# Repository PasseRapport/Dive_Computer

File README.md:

# Freediving Computer

A wrist-mounted freediving computer with tap navigation, wireless charging, and a fully sealed enclosure — no buttons, no external connectors.

---

## V1 — Proof of Concept

Proved two core ideas: **tap-based navigation** via accelerometer and **wireless charging** inside a completely sealed case.

| | |
|---|---|
| **MCU** | ESP32-C3 |
| **Display** | 1.27″ SSD1351 color OLED (128×96) |
| **Pressure** | MS5837-30BA — ±2 mm resolution |
| **Navigation** | LIS2DUX12 tap detection — no buttons |
| **Charging** | LTC4120 wireless receiver — no connectors |
| **Switch** | Magnetic battery cutoff — true 0 µA storage |

### Interface

<p align="center"><em>Tap-based menu navigation — accelerometer detects directional impacts on the casing.</em></p>

### In the Water

<p align="center"><em>Live depth tracking — automatic dive detection and surface recovery timer.</em></p>

### Enclosure

Two-part sandwich assembly sealed by a perimeter O-ring and 12 M2 screws. No dynamic seals anywhere.

---

## V2 — Work in Progress

More compact, better component integration, and additional sensors.

### PCB

### 3D Model

### Exploded View

### Schematic

---

## Repository Structure

```
Dive_Computer/
├── V1/         # Prototype — full firmware + hardware source files
└── V2/         # Current revision — in progress
```

See [`V1/README.md`](V1/README.md) for detailed hardware architecture, firmware design, and dive state machine documentation.

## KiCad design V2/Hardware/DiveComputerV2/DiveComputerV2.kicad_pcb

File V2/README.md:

# Freediving Computer V2

## 3D

## Exploded View

## PCB

## Schematic

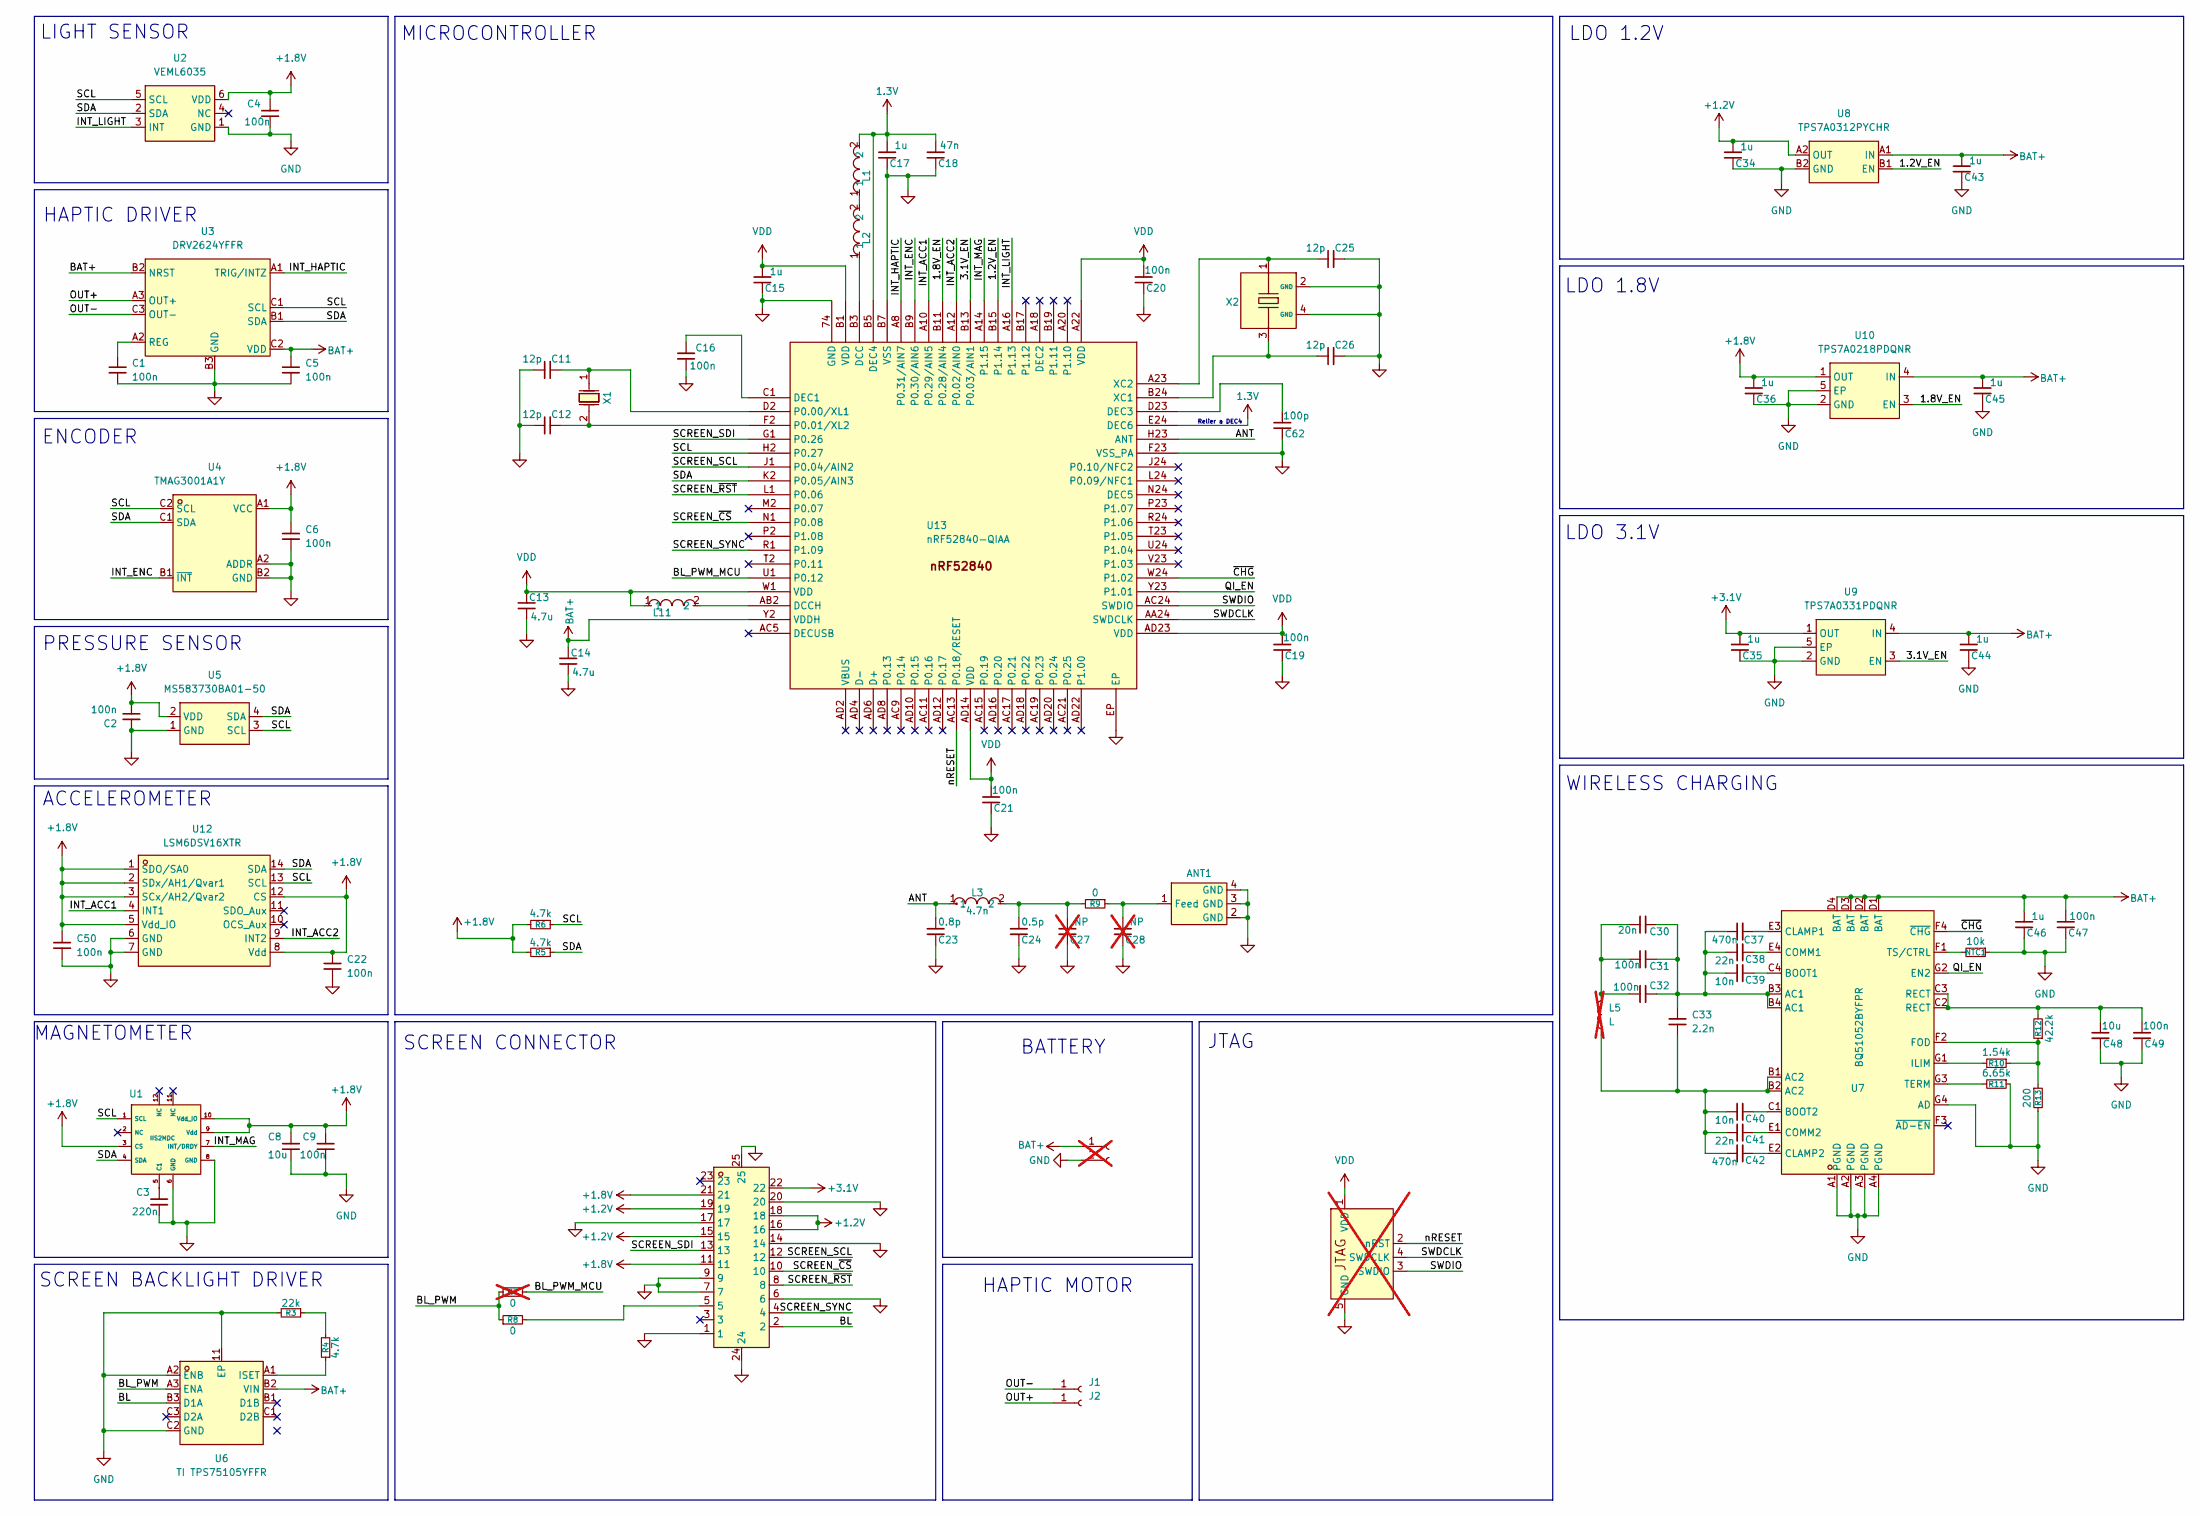
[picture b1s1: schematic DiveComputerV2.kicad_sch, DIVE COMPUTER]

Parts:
ANT1: 2450AT18D0100E; ANT-SMD_4P-L3.2-W1.6; MPN 2450AT18D0100E; LCSC Part C2917718
C1, C2, C4, C5, C6, C9, C22, C47, C50: 100n; C_0402_1005Metric; MPN CL05B104KO5NNNC; LCSC Part C1525
C3: 220n; C_0402_1005Metric; MPN CL05B224KO5NNNC; LCSC Part C16772
C8: 10u; C_0402_1005Metric; LCSC Part C15525
C11, C12, C25, C26: 12p; C_0402_1005Metric; MPN 0402CG120J500NT; LCSC Part C1547
C13, C14: 4.7u; C_0402_1005Metric; LCSC Part C23733
C15, C34, C35, C36, C43, C44, C45, C46: 1u; C_0402_1005Metric; MPN CL05A105KA5NQNC; LCSC Part C52923
C16, C19, C20, C21, C49: 100n; C_0402_1005Metric; MPN CL05B104KB54PNC; LCSC Part C307331
C17: 1u; C_0402_1005Metric; MPN TCC0402X7R105K250AT; LCSC Part C53426846
C18: 47n; C_0402_1005Metric; MPN CL05B473KO5NNNC; LCSC Part C307434
C23: 0.8p; C_0402_1005Metric; MPN GJM1555C1HR80WB01D; LCSC Part C88902
C24: 0.5p; C_0402_1005Metric; MPN GJM1555C1HR50WB01D; LCSC Part C76912
C27, C28: NP; C_0402_1005Metric; not fitted
C30: 20n; C_0805_2012Metric; Voltage 50V; Tolerance 1%; MPN GCM21B5C1H203FA16L; LCSC Part C17588990
C31, C32: 100n; C_1206_3216Metric; Voltage 50V; Tolerance 5%; MPN GRM31C5C1H104JA01L; LCSC Part C97946
C33: 2.2n; C_0402_1005Metric; MPN GRM1555C1H222GA01D; LCSC Part C2987940
C37, C42: 470n; C_0402_1005Metric; MPN GRM155R61E474KE01D; LCSC Part C437526
C38, C41: 22n; C_0402_1005Metric; MPN 0402B223K500NT; LCSC Part C1532
C39, C40: 10n; C_0402_1005Metric; MPN GRM155R71H103KA88J; LCSC Part C2840480
C48: 10u; C_0603_1608Metric; MPN CL10A106MA8NRNC; LCSC Part C96446
C62: 100p; C_0402_1005Metric; MPN 0402CG101J500NT; LCSC Part C1546
FPC1: FH35C-23S-0.3SHW; FPC-SMD_23P-P0.60_HRS_FH35C-23S-0.3SHW; MPN FH35C-23S-0.3SHW(50); LCSC Part C2889270
J1, J2: Conn_01x01_Socket; 2292838-3
J3: Conn_01x02_Socket; THT Solder PAD 2pin; not fitted
J5: SAH_Connect; not fitted
L1: LQW15AN15NG00D; IND-SMD_L1.0-W0.5-2; MPN LQW15AN15NG00D; LCSC Part C98055
L2: LQM18DN100M70L; L0603; MPN LQM18DN100M70L; LCSC Part C713281
L3: 4.7n; L0402-RD; MPN LQG15HS4N7B02D; LCSC Part C162543
L5: L; THT Solder PAD 2pin; not fitted
L11: SLM1608100MIT; L_0603_1608Metric; MPN SLM1608100MIT; LCSC Part C2831366
NTC1: 10k; R_0402_1005Metric; MPN NCP15XH103F03RC; LCSC Part C77131
R3: 22k; R_0402_1005Metric; MPN 0402WGF2202TCE; LCSC Part C25768
R4, R5, R6: 4.7k; R_0402_1005Metric; MPN 0402WGF4701TCE; LCSC Part C25900
R7: 0; R_0402_1005Metric; LCSC Part C17168; not fitted
R8, R9: 0; R_0402_1005Metric; LCSC Part C17168
R10: 1.54k; R_0402_1005Metric; MPN CRCW04021K54FKED; LCSC Part C2085404
R11: 6.65k; R_0402_1005Metric; MPN CRCW04026K65FKED; LCSC Part C2076542
R12: 42.2k; R_0402_1005Metric; MPN FRC0402F4222TS; LCSC Part C5126131
R13: 200; R_0402_1005Metric; MPN 0402WGF2000TCE; LCSC Part C25087
U1: IIS2MDC; VLGA-12_L2.0-W2.0-P0.50-BL; MPN IIS2MDCTR; LCSC Part C2655002
U2: VEML6035; SMD-6_L2.0-W2.0-P0.65-BL; MPN VEML6035; LCSC Part C2655158
U3: DRV2624YFFR; DSBGA-9_L1.4-W1.3-R3-C3-P0.40-BL; MPN DRV2624YFFR; LCSC Part C881487
U4: TMAG3001A1Y; BGA-6_L1.3-W0.8-P0.40-TL_PTMAG3001A2YBGR; MPN TMAG3001A1YBGR; LCSC Part C29073186
U5: MS583730BA01-50; SENSOR-SMD_4P-L3.3-W3.3-P2.00-BL; MPN MS583730BA01-50; LCSC Part C2887941
U6: TI TPS75105YFFR; DSBGA-9_L1.4-W1.3-R3-C3-P0.40-BL; MPN TI TPS75105YFFR; LCSC Part C1857508
U7: BQ51052BYFPR; DSBGA-28_L3.0-W1.9-R4-C7-P0.40-BL; MPN BQ51052BYFPR; LCSC Part C2155980
U8: TPS7A0312PYCHR; DSBGA-4_L0.7-W0.7-R2-C2-P0.35-BL; MPN TPS7A0312PYCHR; LCSC Part C3747308
U9: TPS7A0331PDQNR; X2SON-4_L1.0-W1.0-P0.65-TL-EP; MPN TPS7A0331PDQNR; LCSC Part C2864441
U10: TPS7A0218PDQNR; X2SON-4_L1.0-W1.0-P0.65-TL-EP; MPN TPS7A0218PDQNR; LCSC Part C2862166
U12: LSM6DSV16XTR; LGA-14_L3.0-W2.5-P0.50-BR; MPN LSM6DSV16XTR; LCSC Part C5267406
U13: nRF52840-QIAA; Nordic_AQFN-73-1EP_7x7mm_P0.5mm; PART NUMBER nRF52840-QIAA
X1: CM8V-T1A-32.768KHZ-9PF-20PPM-TB-QC; CRYSTAL-SMD_L2.0-W1.2; MPN CM8V-T1A-32.768kHz-9pF-20PPM-TB-QC; LCSC Part C5280691
X2: ECS-320-CDX-2152; CRYSTAL-SMD_4P-L1.6-W1.2-BL; MPN ECS-320-CDX-2152; LCSC Part C5686354

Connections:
1.3V: C17.2, C18.2, L1.2, U13.B5 (DEC4), U13.E24 (DEC6)
+1.2V: C34.2, FPC1.15, FPC1.16, FPC1.18, FPC1.19, U8.A2 (OUT)
+1.8V: C2.2, C4.1, C6.2, C8.1, C9.1, C22.1, C36.2, C50.2, FPC1.11, FPC1.21, R5.2, R6.2, U1.3 (CS), U1.9 (Vdd), U1.10 (Vdd_IO), U2.6 (VDD), U4.A1 (VCC), U5.2 (VDD), U10.1 (OUT), U12.1 (SDO/SA0), U12.2 (SDx/AH1/Qvar1), U12.3 (SCx/AH2/Qvar2), U12.5 (Vdd_IO), U12.8 (Vdd), U12.12 (CS)
+3.1V: C35.2, FPC1.22, U9.1 (OUT)
/1.2V_EN: U8.B1 (EN), U13.B15 (P1.14)
/1.8V_EN: U10.3 (EN), U13.B11 (P0.28/AIN4)
/3.1V_EN: U9.3 (EN), U13.B13 (P0.03/AIN1)
/ANT: C23.2, L3.1, U13.H23 (ANT)
/BL: FPC1.2, U6.B3 (D1A)
/BL_PWM: R7.1, R8.1, U6.A3 (ENA)
/BL_PWM_MCU: R7.2, U13.U1 (P0.12)
/INT_ACC1: U12.4 (INT1), U13.A10 (P0.29/AIN5)
/INT_ACC2: U12.9 (INT2), U13.A12 (P0.02/AIN0)
/INT_ENC: U4.B1 (~INT), U13.B9 (P0.30/AIN6)
/INT_HAPTIC: U3.A1 (TRIG/INTZ), U13.A8 (P0.31/AIN7)
/INT_LIGHT: U2.3 (INT), U13.A16 (P1.13)
/INT_MAG: U1.7 (INT/DRDY), U13.A14 (P1.15)
/OUT+: J2.1 (Pin_1_1), U3.A3 (OUT+)
/OUT-: J1.1 (Pin_1_1), U3.C3 (OUT-)
/QI_EN: U7.G2 (EN2), U13.Y23 (P1.01)
/SCL: R6.1, U1.1 (SCL), U2.5 (SCL), U3.C1 (SCL), U4.C2 (SCL), U5.3 (SCL), U12.13 (SCL), U13.H2 (P0.27)
/SCREEN_SCL: FPC1.12, U13.J1 (P0.04/AIN2)
/SCREEN_SDI: FPC1.13, U13.G1 (P0.26)
/SCREEN_SYNC: FPC1.4, U13.R1 (P1.09)
/SCREEN_~CS: FPC1.10, U13.N1 (P0.08)
/SCREEN_~RST: FPC1.8, U13.L1 (P0.06)
/SDA: R5.1, U1.4 (SDA), U2.2 (SDA), U3.B1 (SDA), U4.C1 (SDA), U5.4 (SDA), U12.14 (SDA), U13.K2 (P0.05/AIN3)
/SWDCLK: J5.4 (SWDCLK), U13.AA24 (SWDCLK)
/SWDIO: J5.3 (SWDIO), U13.AC24 (SWDIO)
/nRESET: J5.2 (nRST), U13.AC13 (P0.18/RESET)
/~CHG: U7.F4 (~CHG), U13.W24 (P1.02)
BAT+: C5.1, C14.1, C43.2, C44.2, C45.2, C46.2, C47.2, J3.1, U3.B2 (NRST), U3.C2 (VDD), U6.B2 (VIN), U7.D1 (BAT), U7.D2 (BAT), U7.D3 (BAT), U7.D4 (BAT), U8.A1 (IN), U9.4 (IN), U10.4 (IN), U13.Y2 (VDDH)
GND: ANT1.2 (GND), ANT1.3 (GND), ANT1.4 (GND), C1.2, C2.1, C3.2, C4.2, C5.2, C6.1, C8.2, C9.2, C11.2, C12.2, C13.2, C14.2, C15.1, C16.2, C17.1, C18.1, C19.1, C20.1, C21.1, C22.2, C23.1, C24.1, C25.1, C26.1, C27.1, C28.1, C34.1, C35.1, C36.1, C43.1, C44.1, C45.1, C46.1, C47.1, C48.1, C49.1, C50.1, C62.1, FPC1.1, FPC1.6, FPC1.7, FPC1.9, FPC1.14, FPC1.17, FPC1.20, FPC1.24, FPC1.25, J3.2, J5.5 (GND), NTC1.1, R3.2, R11.1, R13.2, U1.6 (GND), U1.8 (GND), U2.1 (GND), U3.B3 (GND), U4.A2 (ADDR), U4.B2 (GND), U5.1 (GND), U6.11 (EP), U6.A2 (ENB), U6.C2 (GND), U7.A1 (PGND), U7.A2 (PGND), U7.A3 (PGND), U7.A4 (PGND), U7.G4 (AD), U8.B2 (GND), U9.2 (GND), U9.5 (EP), U10.2 (GND), U10.5 (EP), U12.6 (GND), U12.7 (GND), U13.74 (GND), U13.B7 (VSS), U13.EP, U13.F23 (VSS_PA), X2.2 (GND), X2.4 (GND)
unnamed: ANT1.1 (Feed), C28.2, R9.1
unnamed: C24.2, C27.2, L3.2, R9.2
unnamed: C30.1, C31.1, C32.1, L5.2
unnamed: C30.2, C31.2, C32.2, C33.1, C37.1, C38.1, C39.1, U7.B3 (AC1), U7.B4 (AC1)
unnamed: C33.2, C40.1, C41.1, C42.1, L5.1, U7.B1 (AC2), U7.B2 (AC2)
unnamed: C48.2, C49.2, R12.2, U7.C2 (RECT), U7.C3 (RECT)
unnamed: FPC1.5, R8.2
unnamed: L1.1, L2.2
unnamed: R3.1, R4.2
unnamed: C3.1, U1.5 (C1)
unnamed: C1.1, U3.A2 (REG)
unnamed: R4.1, U6.A1 (ISET)
unnamed: C39.2, U7.C4 (BOOT1)
unnamed: C40.2, U7.C1 (BOOT2)
unnamed: C37.2, U7.E3 (CLAMP1)
unnamed: C42.2, U7.E2 (CLAMP2)
unnamed: C38.2, U7.E4 (COMM1)
unnamed: C41.2, U7.E1 (COMM2)
unnamed: R10.1, R12.1, R13.1, U7.F2 (FOD)
unnamed: R10.2, U7.G1 (ILIM)
unnamed: R11.2, U7.G3 (TERM)
unnamed: NTC1.2, U7.F1 (TS/CTRL)
unnamed: L2.1, U13.B3 (DCC)
unnamed: L11.2, U13.AB2 (DCCH)
unnamed: C16.1, U13.C1 (DEC1)
unnamed: C62.2, U13.D23 (DEC3)
unnamed: C11.1, U13.D2 (P0.00/XL1), X1.1
unnamed: C12.1, U13.F2 (P0.01/XL2), X1.2
unnamed: C26.2, U13.B24 (XC1), X2.3
unnamed: C25.2, U13.A23 (XC2), X2.1
VDD: C13.1, C15.2, C19.2, C20.2, C21.2, J5.1 (VDD), L11.1, U13.A22 (VDD), U13.AD14 (VDD), U13.AD23 (VDD), U13.B1 (VDD), U13.W1 (VDD)

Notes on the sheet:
PRESSURE SENSOR
MICROCONTROLLER
SCREEN BACKLIGHT DRIVER
BATTERY
SCREEN CONNECTOR
Relier a DEC4
ACCELEROMETER
HAPTIC MOTOR
JTAG
ENCODER
LDO 1.8V
WIRELESS CHARGING
HAPTIC DRIVER
LDO 3.1V
LDO 1.2V
MAGNETOMETER
LIGHT SENSOR

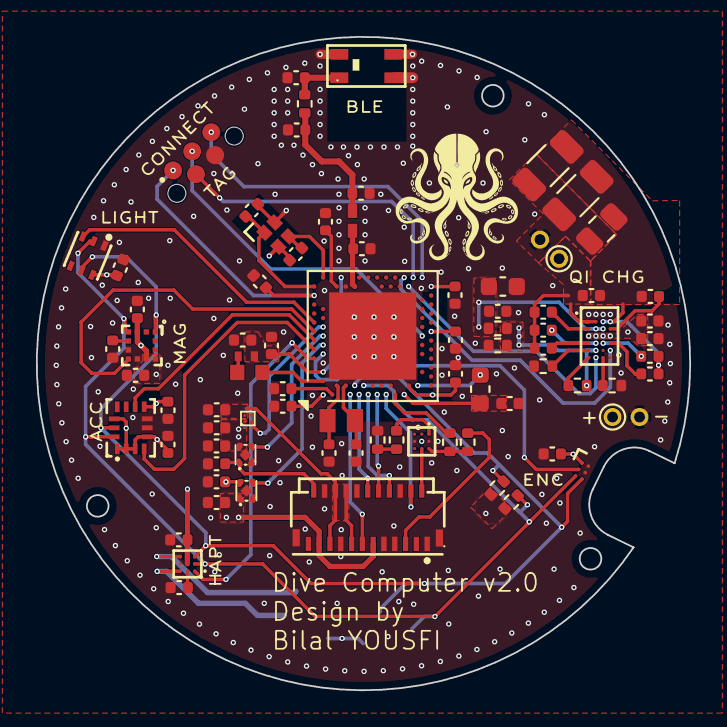
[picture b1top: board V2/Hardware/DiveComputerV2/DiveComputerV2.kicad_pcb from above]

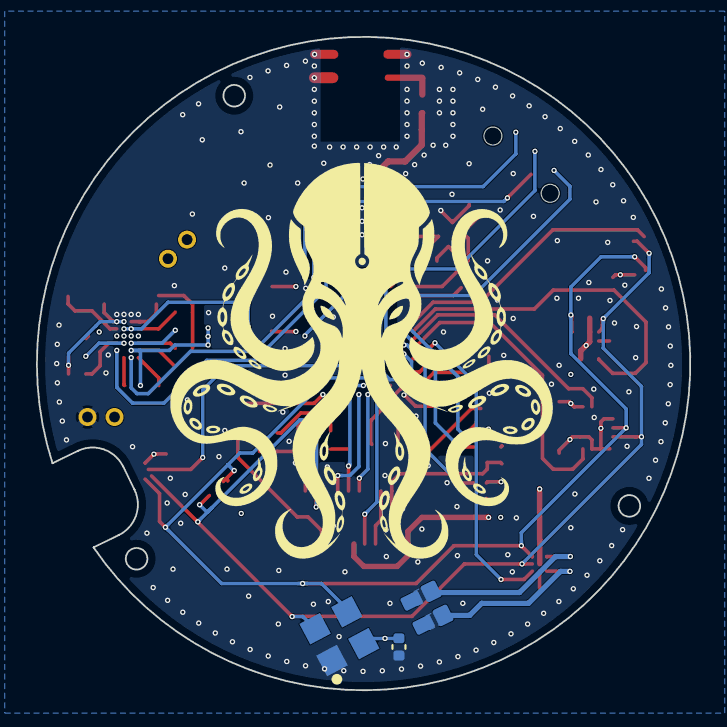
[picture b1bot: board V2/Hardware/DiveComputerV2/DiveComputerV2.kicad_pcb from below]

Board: 4 copper layers, 36.3 x 36.3 mm, 85 parts (4 on the bottom side), 64 nets.

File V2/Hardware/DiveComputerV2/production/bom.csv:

Designator,Footprint,Quantity,Value,LCSC Part #
ANT1,ANT-SMD_4P-L3.2-W1.6,1,2450AT18D0100E,C2917718
"C1, C2, C22, C4, C47, C5, C50, C6, C9",0402,9,100n,C1525
"C11, C12, C25, C26",0402,4,12p,C1547 
"C13, C14",0402,2,4.7u,C23733
"C15, C34, C35, C36, C43, C44, C45, C46",0402,8,1u,C52923
"C16, C19, C20, C21, C49",0402,5,100n,C307331
C17,0402,1,1u,C53426846
C18,0402,1,47n,C307434
C23,0402,1,0.8p,C88902
C24,0402,1,0.5p,C76912
C3,0402,1,220n,C16772
C30,0805,1,20n,C17588990
"C31, C32",1206,2,100n,C97946
C33,0402,1,2.2n,C2987940
"C37, C42",0402,2,470n,C437526
"C38, C41",0402,2,22n,C1532
"C39, C40",0402,2,10n,C2840480
C48,0603,1,10u,C96446
C62,0402,1,100p,C1546
C8,0402,1,10u,C15525
FPC1,FPC-SMD_23P-P0.60_HRS_FH35C-23S-0.3SHW,1,FH35C-23S-0.3SHW,C2889270
L1,IND-SMD_L1.0-W0.5-2,1,LQW15AN15NG00D,C98055
L11,0603,1,SLM1608100MIT,C2831366
L2,L0603,1,LQM18DN100M70L,C713281
L3,L0402-RD,1,4.7n,C162543
NTC1,0402,1,10k,C77131
R10,0402,1,1.54k,C2085404
R11,0402,1,6.65k,C2076542
R12,0402,1,42.2k,C5126131
R13,0402,1,200,C25087
R3,0402,1,22k,C25768
"R4, R5, R6",0402,3,4.7k,C25900
"R8, R9",0402,2,0,C17168 
U1,VLGA-12_L2.0-W2.0-P0.50-BL,1,IIS2MDC,C2655002
U10,X2SON-4_L1.0-W1.0-P0.65-TL-EP,1,TPS7A0218PDQNR,C2862166
U12,LGA-14_L3.0-W2.5-P0.50-BR,1,LSM6DSV16XTR,C5267406
U13,Nordic_AQFN-73-1EP_7x7mm_P0.5mm,1,nRF52840-QIAA,
U2,SMD-6_L2.0-W2.0-P0.65-BL,1,VEML6035,C2655158
U3,DSBGA-9_L1.4-W1.3-R3-C3-P0.40-BL,1,DRV2624YFFR,C881487
U4,BGA-6_L1.3-W0.8-P0.40-TL_PTMAG3001A2YBGR,1,TMAG3001A1Y,C29073186
U5,SENSOR-SMD_4P-L3.3-W3.3-P2.00-BL,1,MS583730BA01-50,C2887941
U6,DSBGA-9_L1.4-W1.3-R3-C3-P0.40-BL,1,TI TPS75105YFFR,C1857508
U7,DSBGA-28_L3.0-W1.9-R4-C7-P0.40-BL,1,BQ51052BYFPR,C2155980
U8,DSBGA-4_L0.7-W0.7-R2-C2-P0.35-BL,1,TPS7A0312PYCHR,C3747308
U9,X2SON-4_L1.0-W1.0-P0.65-TL-EP,1,TPS7A0331PDQNR,C2864441
X1,CRYSTAL-SMD_L2.0-W1.2,1,CM8V-T1A-32.768KHZ-9PF-20PPM-TB-QC,C5280691
X2,CRYSTAL-SMD_4P-L1.6-W1.2-BL,1,ECS-320-CDX-2152,C5686354

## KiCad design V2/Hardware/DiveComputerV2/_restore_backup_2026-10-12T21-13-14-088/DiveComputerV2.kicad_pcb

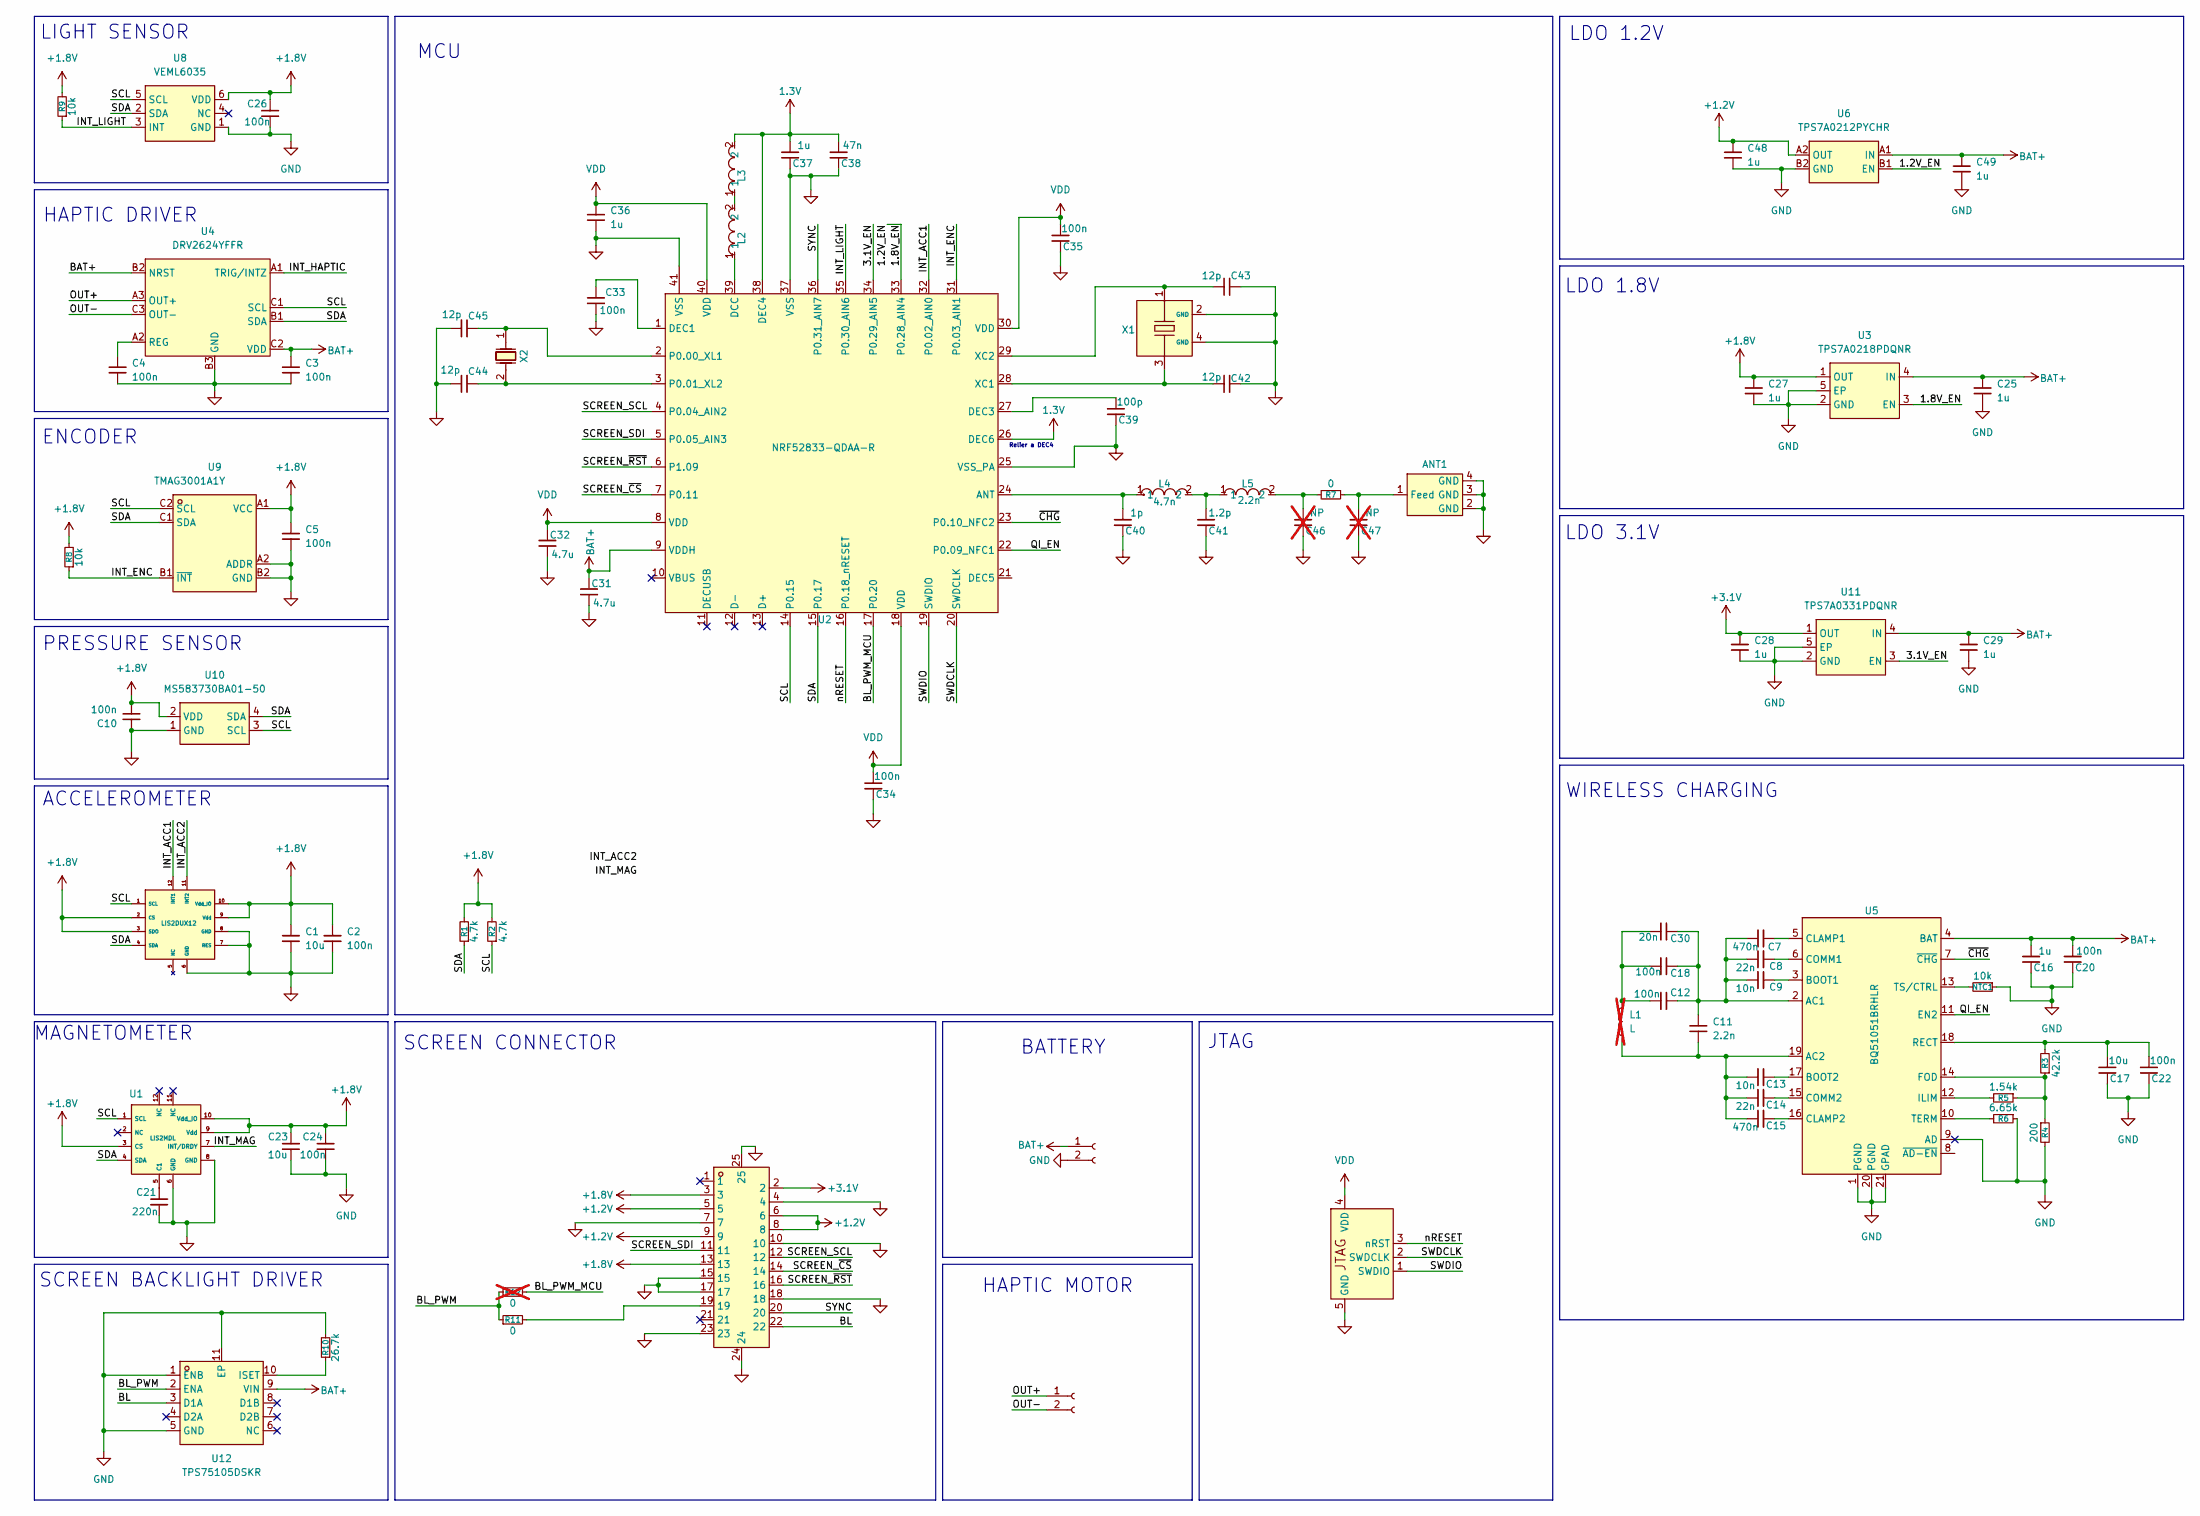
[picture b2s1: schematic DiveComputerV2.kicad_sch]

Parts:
ANT1: 2450AT18D0100E; ANT-SMD_4P-L3.2-W1.6; MPN 2450AT18D0100E; LCSC Part C2917718
BATTERY1: BAT; Hirose_DF13-02P-1.25DSA_1x02_P1.25mm_Vertical
C1, C23: 10u; C_0402_1005Metric; MPN CL05A106MP5NUNC; LCSC Part C315248
C2, C3, C4, C5, C10, C20, C24, C26: 100n; C_0402_1005Metric; MPN CL05B104KO5NNNC; LCSC Part C1525
C6: SAH_Connect
C7, C15: 470n; C_0402_1005Metric; MPN GRM155R61E474KE01D; LCSC Part C437526
C8, C14: 22n; C_0402_1005Metric; MPN 0402B223K500NT; LCSC Part C1532
C9, C13: 10n; C_0402_1005Metric; MPN GRM155R71H103KA88J; LCSC Part C2840480
C11: 2.2n; C_0402_1005Metric; MPN GRM1555C1H222GA01D; LCSC Part C2987940
C12, C18: 100n; C_1206_3216Metric; Voltage 50V; Tolerance 5%; MPN GRM31C5C1H104JA01L; LCSC Part C97946
C16, C25, C27, C28, C29, C36, C48, C49: 1u; C_0402_1005Metric; MPN CL05A105KO5NNNC; LCSC Part C29266
C17: 10u; C_0603_1608Metric; MPN CL10A106MA8NRNC; LCSC Part C96446
C21: 220n; C_0402_1005Metric; MPN CL05B224KO5NNNC; LCSC Part C16772
C22, C33, C34, C35: 100n; C_0402_1005Metric; MPN CL05B104KB54PNC; LCSC Part C307331
C30: 20n; C_0805_2012Metric; Voltage 50V; Tolerance 1%; MPN GCM21B5C1H203FA16L; LCSC Part C17588990
C31, C32: 4.7u; C_0402_1005Metric; MPN CL05A475KP5NRNC; LCSC Part C368809
C37: 1u; C_0402_1005Metric; MPN TCC0402X7R105K250AT; LCSC Part C53426846
C38: 47n; C_0402_1005Metric; MPN CL05B473KO5NNNC; LCSC Part C307434
C39: 100p; C_0402_1005Metric; MPN CC0402KRX7R9BB101; LCSC Part C281751
C40: 1p; C_0402_1005Metric; MPN GJM1555C1H1R0WB01D; LCSC Part C72134
C41: 1.2p; C_0402_1005Metric; MPN GJM1555C1H1R2WB01D; LCSC Part C76899
C42, C43, C44, C45: 12p; C_0402_1005Metric; MPN CC0402GRNPO9BN120; LCSC Part C526985
C46, C47: NP; C_0402_1005Metric; not fitted
FPC1: FH35C-23S-0.3SHW; FPC-SMD_23P-P0.60_HRS_FH35C-23S-0.3SHW; MPN FH35C-23S-0.3SHW(50); LCSC Part C2889270
HAPTIC_MOTOR1: BAT; Hirose_DF13-02P-1.25DSA_1x02_P1.25mm_Vertical
L1: L; L_Axial_L5.3mm_D2.2mm_P2.54mm_Vertical_Vishay_IM-1; not fitted
L2: LQM18DN100M70L; L0603; MPN LQM18DN100M70L; LCSC Part C713281
L3: LQW15AN15NG00D; IND-SMD_L1.0-W0.5-2; MPN LQW15AN15NG00D; LCSC Part C98055
L4: 4.7n; L0402-RD; MPN LQG15HS4N7B02D; LCSC Part C162543
L5: 2.2n; L0402; MPN LQG15HS2N2B02D; LCSC Part C162540
LIS2DUX12: LGA-12_2x2mm_P0.5mm; LCSC Part C17548754
NTC1: 10k; R_0402_1005Metric; MPN NCP15XH103F03RC; LCSC Part C77131
R1, R2: 4.7k; R_0402_1005Metric; MPN 0402WGF4701TCE; LCSC Part C25900
R3: 42.2k; R_0402_1005Metric; MPN FRC0402F4222TS; LCSC Part C5126131
R4: 200; R_0402_1005Metric; MPN 0402WGF2000TCE; LCSC Part C25087
R5: 1.54k; R_0402_1005Metric; MPN CRCW04021K54FKED; LCSC Part C2085404
R6: 6.65k; R_0402_1005Metric; MPN CRCW04026K65FKED; LCSC Part C2076542
R7, R11: 0; R_0402_1005Metric; MPN RC0402JR-070RL; LCSC Part C60485
R8, R9: 10k; R_0402_1005Metric; MPN 0402WGF1002TCE; LCSC Part C25744
R10: 26.7k; R_0402_1005Metric; MPN RC-02K2672FT; LCSC Part C324918
R12: 0; R_0402_1005Metric; MPN RC0402JR-070RL; LCSC Part C60485; not fitted
U1: LIS2MDL; VLGA-12_L2.0-W2.0-P0.50-BL; MPN LIS2MDLTR; LCSC Part C919695
U2: NRF52833-QDAA-R; QFN-40_L5.0-W5.0-P0.40-TL-EP3.6; MPN nRF52833-QDAA-R; LCSC Part C2895249
U3: TPS7A0218PDQNR; X2SON-4_L1.0-W1.0-P0.65-TL-EP; MPN TPS7A0218PDQNR; LCSC Part C2862166
U4: DRV2624YFFR; DSBGA-9_L1.4-W1.3-R3-C3-P0.40-BL; MPN DRV2624YFFR; LCSC Part C881487
U5: BQ51051BRHLR; VQFN-20_L4.5-W3.5-P0.50-BL-EP_BQ24100RHLR; MPN BQ51051BRHLR; LCSC Part C2876732
U6: TPS7A0212PYCHR; DSBGA-4_L0.7-W0.7-R2-C2-P0.35-BL; MPN TPS7A0212PYCHR; LCSC Part C2918962
U8: VEML6035; SMD-6_L2.0-W2.0-P0.65-BL; MPN VEML6035; LCSC Part C2655158
U9: TMAG3001A1Y; BGA-6_L1.3-W0.8-P0.40-TL_PTMAG3001A2YBGR; MPN TMAG3001A1YBGR; LCSC Part C29073186
U10: MS583730BA01-50; SENSOR-SMD_4P-L3.3-W3.3-P2.00-BL; MPN MS583730BA01-50; LCSC Part C2887941
U11: TPS7A0331PDQNR; X2SON-4_L1.0-W1.0-P0.65-TL-EP; MPN TPS7A0331PDQNR; LCSC Part C2864441
U12: TPS75105DSKR; WSON-10_L2.5-W2.5-W0.50-TL-EP; MPN TPS75105DSKR; LCSC Part C2859928
X1: ECS-320-CDX-2152; CRYSTAL-SMD_4P-L1.6-W1.2-BL; MPN ECS-320-CDX-2152; LCSC Part C5686354
X2: CM8V-T1A-32.768KHZ-9PF-20PPM-TB-QC; CRYSTAL-SMD_L2.0-W1.2; MPN CM8V-T1A-32.768kHz-9pF-20PPM-TB-QC; LCSC Part C5280691

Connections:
1.3V: C37.2, C38.2, L3.2, U2.26 (DEC6), U2.38 (DEC4)
+1.2V: C48.1, FPC1.5, FPC1.6, FPC1.8, FPC1.9, U6.A2 (OUT)
+1.8V: C1.1, C2.1, C5.2, C10.2, C23.1, C24.1, C26.1, C27.1, FPC1.3, FPC1.13, LIS2DUX12.2 (CS), LIS2DUX12.3 (SDO), LIS2DUX12.9 (Vdd), LIS2DUX12.10 (Vdd_IO), R1.2, R2.2, R8.2, R9.2, U1.3 (CS), U1.9 (Vdd), U1.10 (Vdd_IO), U3.1 (OUT), U8.6 (VDD), U9.A1 (VCC), U10.2 (VDD)
+3.1V: C28.1, FPC1.2, U11.1 (OUT)
/1.2V_EN: U2.33 (P0.28_AIN4), U3.3 (EN), U6.B1 (EN)
/3.1V_EN: U2.34 (P0.29_AIN5), U11.3 (EN)
/BL: FPC1.22, U12.3 (D1A)
/BL_PWM: R11.1, R12.1, U12.2 (ENA)
/BL_PWM_MCU: R12.2, U2.17 (P0.20)
/INT_ACC1: LIS2DUX12.12 (INT1), U2.32 (P0.02_AIN0)
/INT_ACC2: LIS2DUX12.11 (INT2)
/INT_ENC: R8.1, U2.31 (P0.03_AIN1), U9.B1 (~INT)
/INT_HAPTIC: U4.A1 (TRIG/INTZ)
/INT_LIGHT: R9.1, U2.35 (P0.30_AIN6), U8.3 (INT)
/INT_MAG: U1.7 (INT/DRDY)
/OUT+: HAPTIC_MOTOR1.1, U4.A3 (OUT+)
/OUT-: HAPTIC_MOTOR1.2, U4.C3 (OUT-)
/QI_EN: U2.22 (P0.09_NFC1), U5.11 (EN2)
/SCL: LIS2DUX12.1 (SCL), R2.1, U1.1 (SCL), U2.14 (P0.15), U4.C1 (SCL), U8.5 (SCL), U9.C2 (SCL), U10.3 (SCL)
/SCREEN_SCL: FPC1.12, U2.4 (P0.04_AIN2)
/SCREEN_SDI: FPC1.11, U2.5 (P0.05_AIN3)
/SCREEN_~CS: FPC1.14, U2.7 (P0.11)
/SCREEN_~RST: FPC1.16, U2.6 (P1.09)
/SDA: LIS2DUX12.4 (SDA), R1.1, U1.4 (SDA), U2.15 (P0.17), U4.B1 (SDA), U8.2 (SDA), U9.C1 (SDA), U10.4 (SDA)
/SWDCLK: C6.2 (SWDCLK), U2.20 (SWDCLK)
/SWDIO: C6.1 (SWDIO), U2.19 (SWDIO)
/SYNC: FPC1.20, U2.36 (P0.31_AIN7)
/nRESET: C6.3 (nRST), U2.16 (P0.18_nRESET)
/~CHG: U2.23 (P0.10_NFC2), U5.7 (~CHG)
BAT+: BATTERY1.1, C3.1, C16.2, C20.2, C25.1, C29.1, C31.1, C49.1, U2.9 (VDDH), U3.4 (IN), U4.B2 (NRST), U4.C2 (VDD), U5.4 (BAT), U6.A1 (IN), U11.4 (IN), U12.9 (VIN)
GND: ANT1.2 (GND), ANT1.3 (GND), ANT1.4 (GND), BATTERY1.2, C1.2, C2.2, C3.2, C4.2, C5.1, C6.5 (GND), C10.1, C16.1, C17.1, C20.1, C21.2, C22.1, C23.2, C24.2, C25.2, C26.2, C27.2, C28.2, C29.2, C31.2, C32.2, C33.2, C34.1, C35.1, C36.1, C37.1, C38.1, C39.1, C40.1, C41.1, C42.1, C43.1, C44.2, C45.2, C46.1, C47.1, C48.2, C49.2, FPC1.4, FPC1.7, FPC1.10, FPC1.15, FPC1.17, FPC1.18, FPC1.23, FPC1.24, FPC1.25, LIS2DUX12.6 (GND), LIS2DUX12.7 (RES), LIS2DUX12.8 (GND), NTC1.1, R4.2, R6.1, R10.2, U1.6 (GND), U1.8 (GND), U2.25 (VSS_PA), U2.37 (VSS), U2.41 (VSS), U3.2 (GND), U3.5 (EP), U4.B3 (GND), U5.1 (PGND), U5.9 (AD), U5.20 (PGND), U5.21 (GPAD), U6.B2 (GND), U8.1 (GND), U9.A2 (ADDR), U9.B2 (GND), U10.1 (GND), U11.2 (GND), U11.5 (EP), U12.1 (ENB), U12.5 (GND), U12.11 (EP), X1.2 (GND), X1.4 (GND)
unnamed: ANT1.1 (Feed), C47.2, R7.1
unnamed: C12.1, C18.1, C30.1, L1.2
unnamed: C41.2, L4.2, L5.1
unnamed: C46.2, L5.2, R7.2
unnamed: FPC1.19, R11.2
unnamed: L2.2, L3.1
unnamed: C21.1, U1.5 (C1)
unnamed: C40.2, L4.1, U2.24 (ANT)
unnamed: L2.1, U2.39 (DCC)
unnamed: C33.1, U2.1 (DEC1)
unnamed: C39.2, U2.27 (DEC3)
unnamed: C45.1, U2.2 (P0.00_XL1), X2.1
unnamed: C44.1, U2.3 (P0.01_XL2), X2.2
unnamed: C42.2, U2.28 (XC1), X1.3
unnamed: C43.2, U2.29 (XC2), X1.1
unnamed: C4.1, U4.A2 (REG)
unnamed: C7.1, C8.1, C9.1, C11.1, C12.2, C18.2, C30.2, U5.2 (AC1)
unnamed: C11.2, C13.1, C14.1, C15.1, L1.1, U5.19 (AC2)
unnamed: C9.2, U5.3 (BOOT1)
unnamed: C13.2, U5.17 (BOOT2)
unnamed: C7.2, U5.5 (CLAMP1)
unnamed: C15.2, U5.16 (CLAMP2)
unnamed: C8.2, U5.6 (COMM1)
unnamed: C14.2, U5.15 (COMM2)
unnamed: R3.1, R4.1, R5.1, U5.14 (FOD)
unnamed: R5.2, U5.12 (ILIM)
unnamed: C17.2, C22.2, R3.2, U5.18 (RECT)
unnamed: R6.2, U5.10 (TERM)
unnamed: NTC1.2, U5.13 (TS/CTRL)
unnamed: R10.1, U12.10 (ISET)
VDD: C6.4 (VDD), C32.1, C34.2, C35.2, C36.2, U2.8 (VDD), U2.18 (VDD), U2.30 (VDD), U2.40 (VDD)

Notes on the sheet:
PRESSURE SENSOR
MCU
SCREEN BACKLIGHT DRIVER
BATTERY
SCREEN CONNECTOR
ACCELEROMETER
HAPTIC MOTOR
JTAG
ENCODER
LDO 1.8V
WIRELESS CHARGING
HAPTIC DRIVER
LDO 3.1V
LDO 1.2V
MAGNETOMETER
Relier a DEC4
LIGHT SENSOR

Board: 4 copper layers, 84 parts (1 on the bottom side), 59 nets, no tracks yet.
